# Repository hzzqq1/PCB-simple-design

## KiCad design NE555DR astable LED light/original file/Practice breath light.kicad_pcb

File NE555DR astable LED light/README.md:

This Pcb design is a simple practice by NE555DR as the main clock with astable circuit. This work as practice which help me to be more familiar with Kicard.This is the schematic.

This is the pcb design(the original design which not add any silkscreen)

pcb design 3D overview

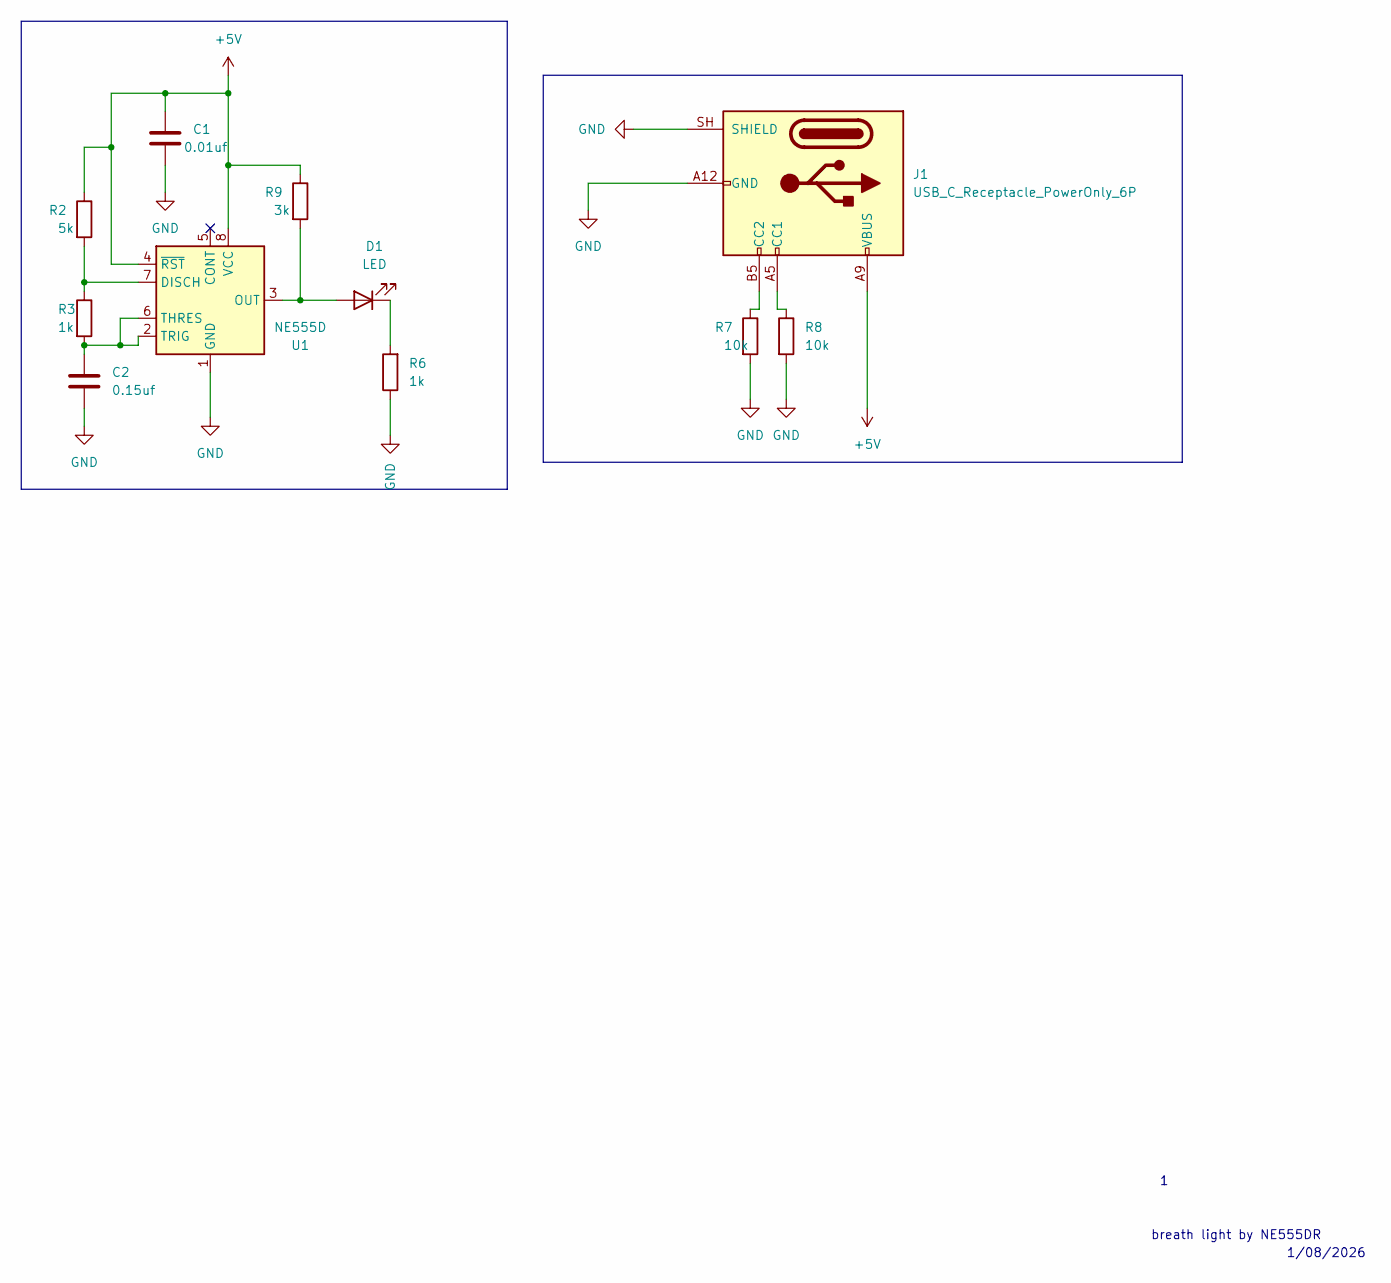
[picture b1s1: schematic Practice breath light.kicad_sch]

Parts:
C1: 0.01uf; C_0805_2012Metric
C2: 0.15uf; C_0805_2012Metric
D1: LED; LED_0805_2012Metric
J1: USB_C_Receptacle_PowerOnly_6P; USB_C_Receptacle_HRO_TYPE-C-31-M-17
R2: 5k; R_0805_2012Metric
R3, R6: 1k; R_0805_2012Metric
R7, R8: 10k; R_0805_2012Metric
R9: 3k; R_0805_2012Metric
U1: NE555D; SOIC-8_3.9x4.9mm_P1.27mm

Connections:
+5V: C1.1, J1.A9 (VBUS), J1.B9 (VBUS), R2.1, R9.1, U1.4 (~RST), U1.8 (VCC)
GND: C1.2, C2.2, J1.A12 (GND), J1.B12 (GND), J1.SH (SHIELD), R6.1, R7.2, R8.2, U1.1 (GND)
unnamed: D1.2 (A), R9.2, U1.3 (OUT)
unnamed: D1.1 (K), R6.2
unnamed: J1.A5 (CC1), R8.1
unnamed: J1.B5 (CC2), R7.1
unnamed: R2.2, R3.1, U1.7 (DISCH)
unnamed: C2.1, R3.2, U1.2 (TRIG), U1.6 (THRES)

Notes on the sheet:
breath light by NE555DR
1/08/2026

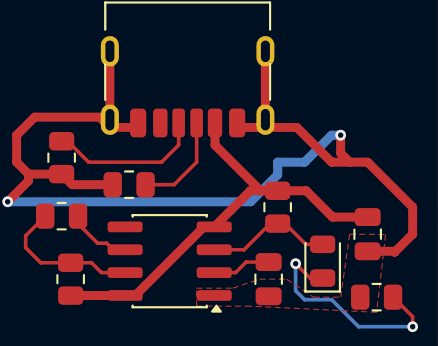
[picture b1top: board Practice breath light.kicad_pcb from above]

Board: 2 copper layers, 11 parts (0 on the bottom side), 8 nets.
